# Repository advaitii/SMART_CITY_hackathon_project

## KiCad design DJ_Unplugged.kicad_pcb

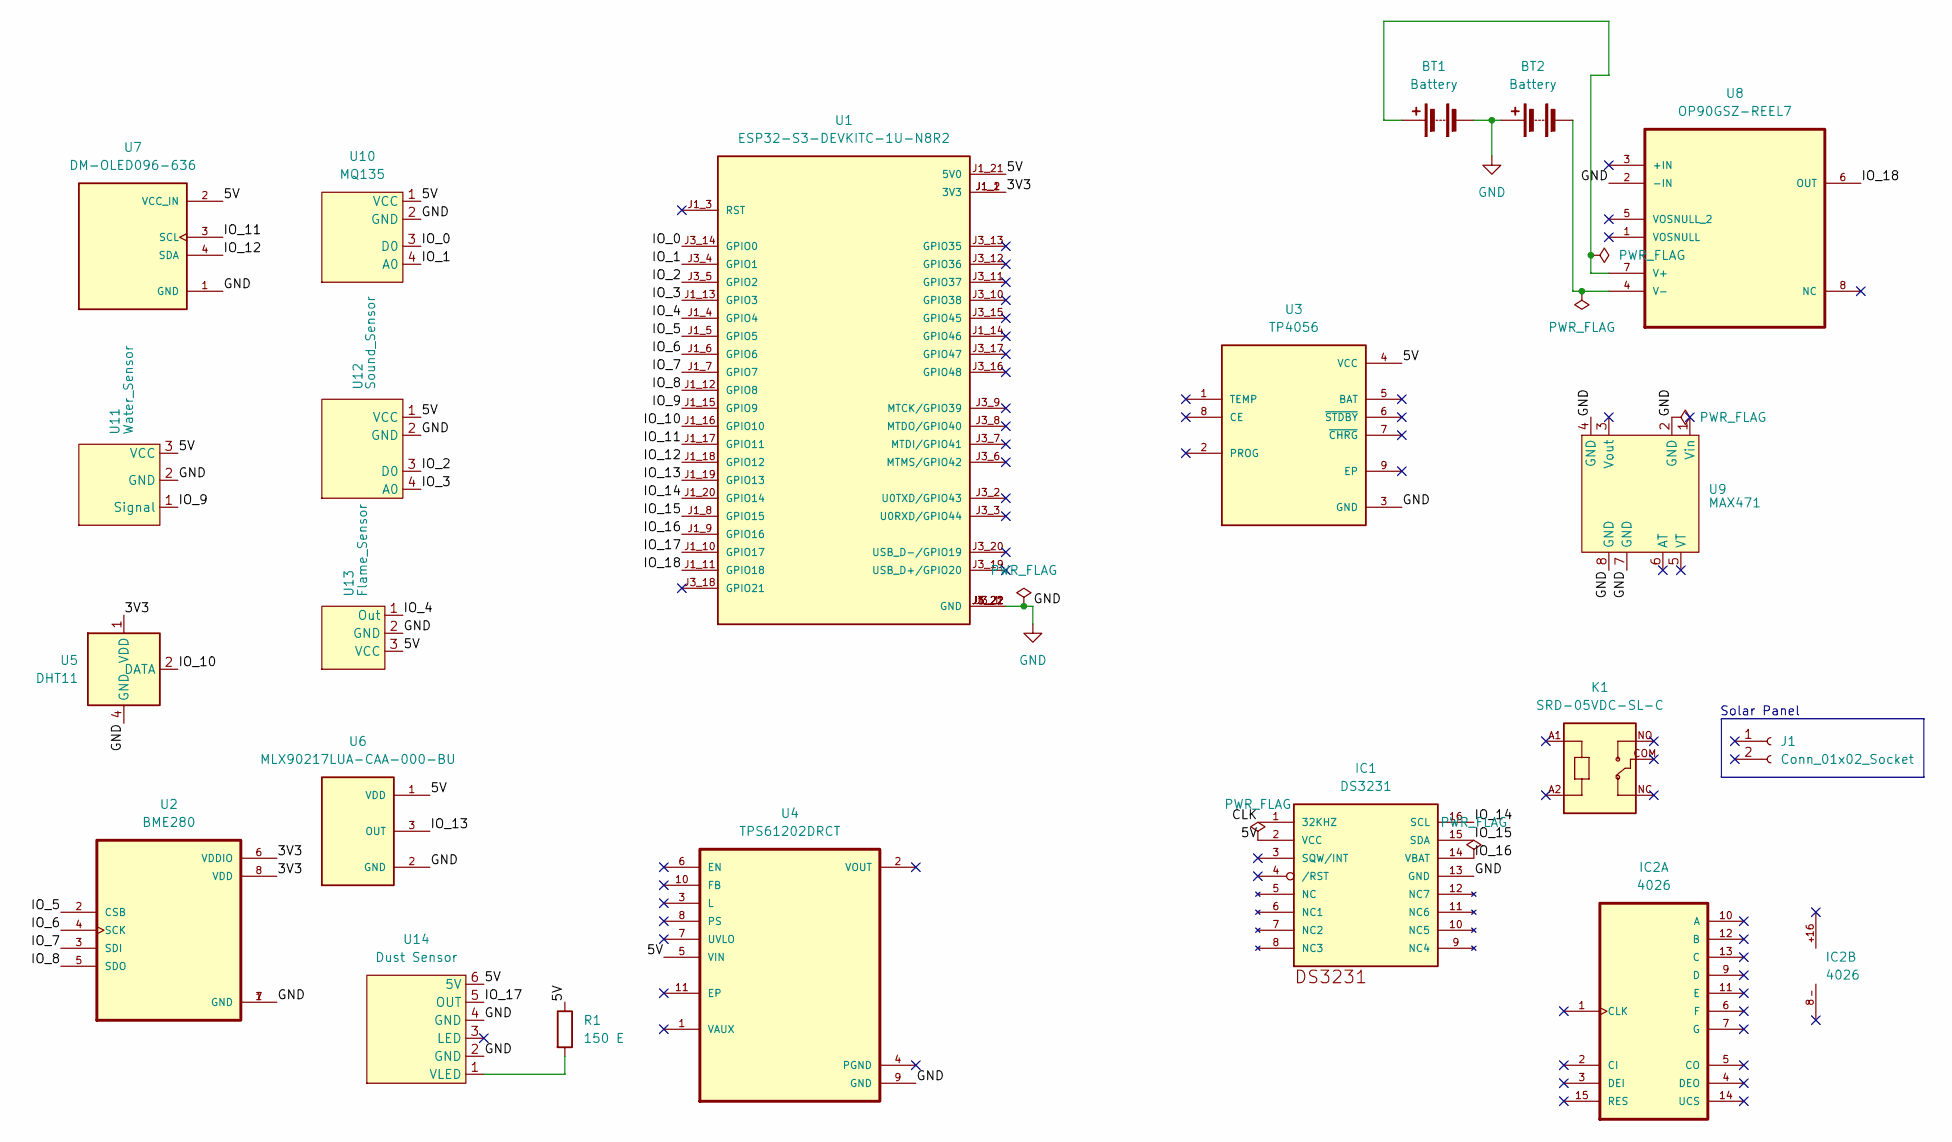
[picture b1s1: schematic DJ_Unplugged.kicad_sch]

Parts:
BT1, BT2: Battery; BatteryHolder_Eagle_12BH611-GR
IC1: DS3231; SO16W
IC2: 4026; DIL16
J1: Conn_01x02_Socket; PinHeader_1x02_P2.54mm_Vertical
K1: SRD-05VDC-SL-C; RELAY_SRD-05VDC-SL-C
R1: 150 E
U1: ESP32-S3-DEVKITC-1U-N8R2; XCVR_ESP32-S3-DEVKITC-1U-N8R2; PARTREV 5.3
U2: BME280; PSON65P250X250X100-8N
U3: TP4056; SOP127P600X175-9N
U4: TPS61202DRCT; VREG_V62_16624-01YE
U5: DHT11; Aosong_DHT11_5.5x12.0_P2.54mm
U6: MLX90217LUA-CAA-000-BU; TO92127P410H430-3; PARTREV 010
U7: DM-OLED096-636; MODULE_DM-OLED096-636; PARTREV 2018-09-10
U8: OP90GSZ-REEL7; SOIC127P600X175-8N; MPN OP90GSZ-REEL7; DigiKey_Part_Number 2156-OP90GS-MA-ND
U9: MAX471
U10: MQ135
U11: Water_Sensor; Foot
U12: Sound_Sensor; MQ135
U13: Flame_Sensor; Footprint_IR_Flame
U14: Dust Sensor; Dust

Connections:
/3V3: U1.J1_1 (3V3), U1.J1_2 (3V3), U2.6 (VDDIO), U2.8 (VDD), U5.1 (VDD)
/5V: IC1.2 (VCC), R1.1, U1.J1_21 (5V0), U3.4 (VCC), U4.5 (VIN), U6.1 (VDD), U7.2 (VCC_IN), U10.1 (VCC), U11.3 (VCC), U12.1 (VCC), U13.3 (VCC), U14.6 (5V)
/CLK: IC1.1 (32KHZ)
/IO_0: U1.J3_14 (GPIO0), U10.3 (D0)
/IO_1: U1.J3_4 (GPIO1), U10.4 (A0)
/IO_2: U1.J3_5 (GPIO2), U12.3 (D0)
/IO_3: U1.J1_13 (GPIO3), U12.4 (A0)
/IO_4: U1.J1_4 (GPIO4), U13.1 (Out)
/IO_5: U1.J1_5 (GPIO5), U2.2 (CSB)
/IO_6: U1.J1_6 (GPIO6), U2.4 (SCK)
/IO_7: U1.J1_7 (GPIO7), U2.3 (SDI)
/IO_8: U1.J1_12 (GPIO8), U2.5 (SDO)
/IO_9: U1.J1_15 (GPIO9), U11.1 (Signal)
/IO_10: U1.J1_16 (GPIO10), U5.2 (DATA)
/IO_11: U1.J1_17 (GPIO11), U7.3 (SCL)
/IO_12: U1.J1_18 (GPIO12), U7.4 (SDA)
/IO_13: U1.J1_19 (GPIO13), U6.3 (OUT)
/IO_14: IC1.16 (SCL), U1.J1_20 (GPIO14)
/IO_15: IC1.15 (SDA), U1.J1_8 (GPIO15)
/IO_16: IC1.14 (VBAT), U1.J1_9 (GPIO16)
/IO_17: U1.J1_10 (GPIO17), U14.5 (OUT)
/IO_18: U1.J1_11 (GPIO18), U8.6 (OUT)
GND: BT1.2 (-), BT2.1 (+), IC1.13 (GND), U1.J1_22 (GND), U1.J3_1 (GND), U1.J3_21 (GND), U1.J3_22 (GND), U2.1 (GND), U2.7 (GND), U3.3 (GND), U4.9 (GND), U5.4 (GND), U6.2 (GND), U7.1 (GND), U8.2 (-IN), U9.2 (GND), U9.4 (GND), U9.7 (GND), U9.8 (GND), U10.2 (GND), U11.2 (GND), U12.2 (GND), U13.2 (GND), U14.2 (GND), U14.4 (GND)
unnamed: BT1.1 (+), U8.7 (V+)
unnamed: BT2.2 (-), U8.4 (V-)
unnamed: R1.2, U14.1 (VLED)

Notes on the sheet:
Solar Panel

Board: 2 copper layers, 20 parts (0 on the bottom side), 24 nets, no tracks yet.
